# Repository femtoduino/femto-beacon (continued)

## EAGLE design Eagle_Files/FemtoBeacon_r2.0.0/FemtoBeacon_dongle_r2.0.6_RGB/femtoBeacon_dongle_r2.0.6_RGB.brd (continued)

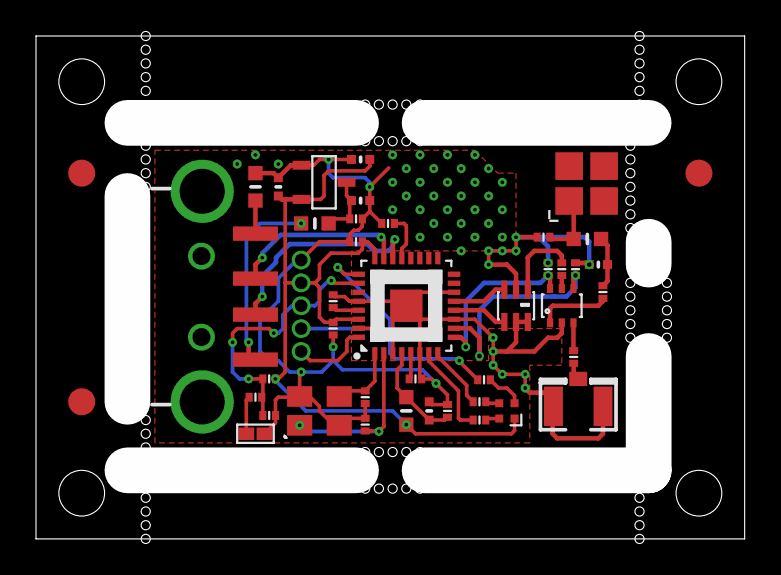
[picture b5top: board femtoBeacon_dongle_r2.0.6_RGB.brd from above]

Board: 2 copper layers, 39.4 x 27.9 mm, 44 parts (0 on the bottom side), 34 nets.

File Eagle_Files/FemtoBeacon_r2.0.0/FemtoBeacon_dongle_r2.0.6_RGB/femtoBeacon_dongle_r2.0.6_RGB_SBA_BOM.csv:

##########################################################################
       Name: Placement Bill of Materials Generator

    Version: 4 (2-sided, top)
         By: Small Batch Assembly
        URL: www.smallbatchassembly.com
 SourceFile: femtoBeacon_dongle_r2.0.6_RGB.brd
   DateTime: 1/3/18 4:22 AM
      Units: inches
##########################################################################
REF,PACKAGE,VALUE,X,Y,ROTATION,
ASWITCH   , AS222-92LF            , AS222-92LF     , 1.1500, 0.5100, 0.0
BTN   , SPST_SMD            , DNP     , 0.4800, 0.2300, 0.0
C1   , PART            , 0.1uF     , 0.5100, 0.2700, 0.0
C2   , PART            , 0.1uF     , 0.7700, 0.6900, 180.0
C5   , _0402MP            , 2.2uF     , 0.7100, 0.8300, 180.0
C6   , _0402MP            , 2.2uF     , 0.7100, 0.7400, 0.0
C7   , PART            , 0.47uF     , 0.7000, 0.7000, 0.0
C8   , PART            , 0.1uF     , 0.9000, 0.2800, 90.0
C9   , PART            , 0.1uF     , 0.6500, 0.5200, 90.0
C10   , PART            , 0.1uF     , 0.7000, 0.6500, 180.0
C11   , _0402MP            , 1.2pF     , 1.2300, 0.6000, 180.0
C13   , PART            , DNP     , 1.1100, 0.6600, 180.0
C14   , PART            , 9pF     , 0.7200, 0.2500, 270.0
C15   , PART            , 9pF     , 0.7200, 0.3100, 270.0
C16   , PART            , 0.1uF     , 0.6500, 0.4600, 270.0
C17   , PART            , 0.1uF     , 0.8300, 0.3500, 0.0
C18   , PART            , 22pF     , 1.1500, 0.5900, 270.0
C19   , PART            , 22pF     , 1.1800, 0.5900, 270.0
C20   , PART            , 22pF     , 1.1200, 0.5900, 90.0
C21   , _0402MP            , 10uF     , 0.5300, 0.7700, 270.0
C22   , _0402MP            , 10uF     , 0.8600, 0.2800, 270.0
C23   , PART            , 22pF     , 1.1760, 0.3980, 90.0
C24   , PART            , 22pF     , 1.2400, 0.5400, 90.0
CN1   , USB_A-SMT            ,      , 0.4800, 0.5300, 90.0
FB1   , _0603MP            ,      , 0.4800, 0.7700, 90.0
FB2   , _0603MP            ,      , 0.6100, 0.6900, 0.0
FID1   , FIDUCIAL_1MM            , FIDUCIAL     , 0.1000, 0.3000, 0.0
FID2   , FIDUCIAL_1MM            , FIDUCIAL     , 0.1000, 0.8000, 0.0
FID3   , FIDUCIAL_1MM            , FIDUCIAL     , 1.4500, 0.8000, 0.0
L1   , _0603MP            , 1.8nH     , 1.2060, 0.6560, 0.0
L6   , _0603MP            , 10uH     , 0.8100, 0.2800, 90.0
LDO_VREG   , MCP1700T-3302E/TT            , MCP1700T-3302E/TT     , 0.6300, 0.7800, 270.0
R1   , PART            , 330     , 0.4800, 0.3100, 0.0
R2   , PART            , 10K     , 0.5100, 0.3500, 0.0
R4   , PART            , 330     , 0.9700, 0.2600, 0.0
R6   , PART            , 330     , 0.9700, 0.3000, 0.0
R7   , PART            , 330     , 0.9800, 0.3480, 0.0
RGBLED   , LRTB_R48G            , LRTB_R48G     , 1.0300, 0.2800, 270.0
U$6   , 0479480001            , 0479480001     , 1.2040, 0.7770, 90.0
U$12   , 0805_BALUN            , JOHANSON_2450BM15A0015E     , 1.0500, 0.5100, 270.0
U$76   , QFN32            , ATSAMR21E18A-MUT     , 0.8100, 0.5100, 90.0
UFLANT   , U.FL            , uFL     , 1.1860, 0.2900, 90.0
XOSCRF   , TSX-3225            , 16MHz     , 0.6200, 0.2800, 0.0

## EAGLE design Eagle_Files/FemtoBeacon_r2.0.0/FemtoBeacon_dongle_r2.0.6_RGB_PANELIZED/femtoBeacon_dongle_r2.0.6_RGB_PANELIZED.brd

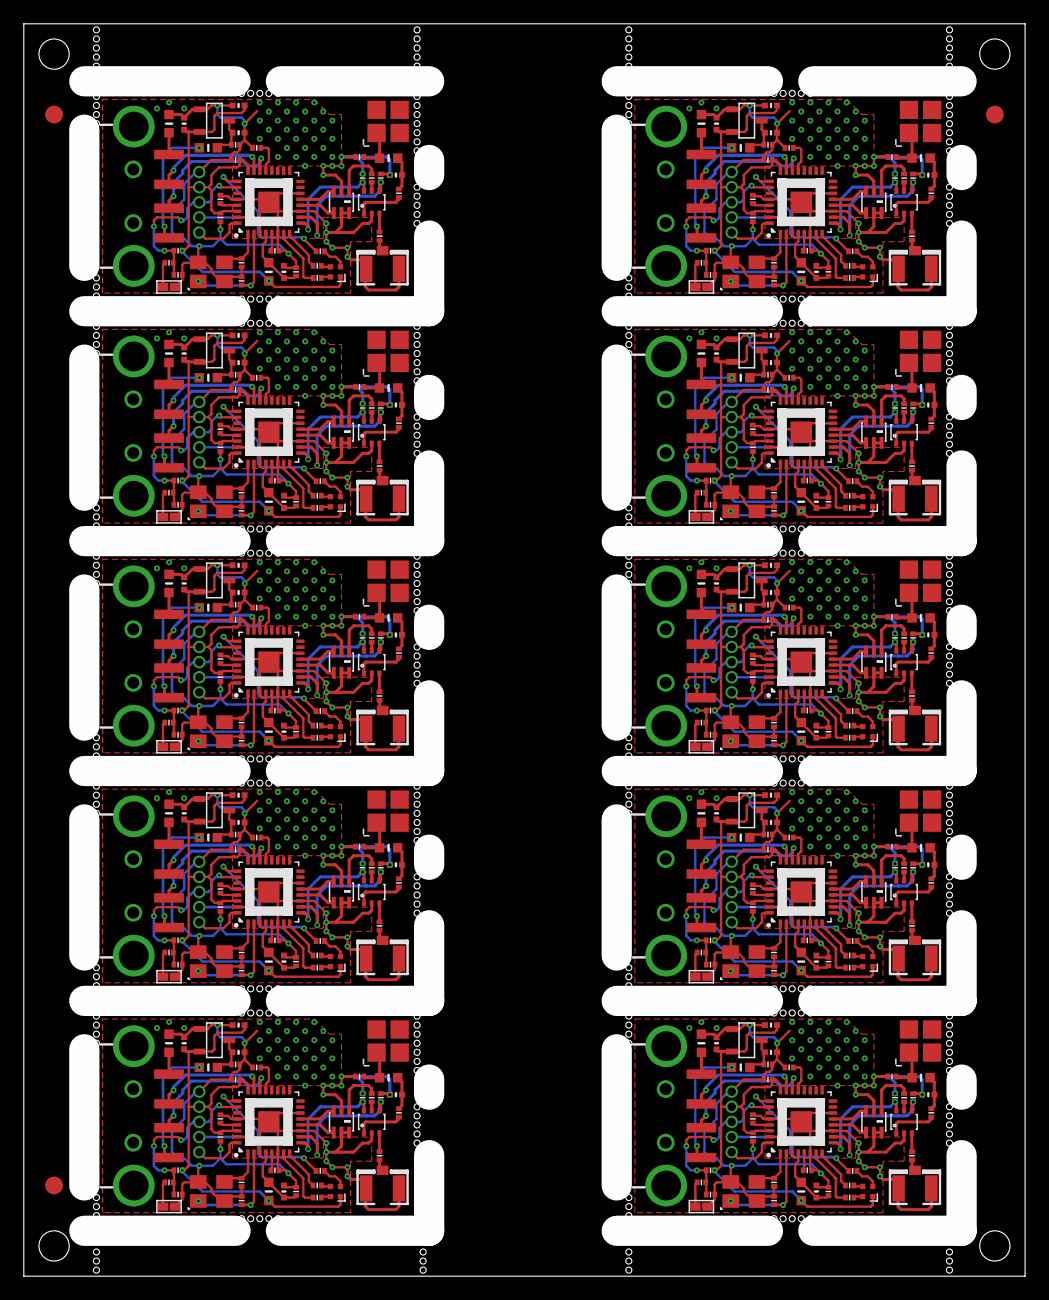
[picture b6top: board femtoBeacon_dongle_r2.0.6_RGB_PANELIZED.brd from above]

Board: 2 copper layers, 84.1 x 105.2 mm, 413 parts (0 on the bottom side), 340 nets.

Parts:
ASWITCH, ASWITCH1, ASWITCH2, ASWITCH3, ASWITCH4, ASWITCH5, ASWITCH6, ASWITCH7, ASWITCH8, ASWITCH9: AS222-92LF
BTN, BTN1, BTN2, BTN3, BTN4, BTN5, BTN6, BTN7, BTN8, BTN9: DNP; SPST_SMD
C1, C2, C3, C4, C8, C9, C10, C16, C17, C27, C28, C29, C35, C36, C43, C44, C48, C49, C50, C56, C57, C64, C65, C69, C70, C71, C77, C78, C85, C86, C90, C91, C92, C98, C99, C106, C107, C111, C112, C113, C119, C120, C127, C128, C132, C133, C134, C140, C141, C148, C149, C153, C154, C155, C161, C162, C169, C170, C174, C175, C176, C182, C183, C190, C191, C195, C196, C197, C203, C204: 0.1uF; PART
C5, C6, C32, C33, C53, C54, C74, C75, C95, C96, C116, C117, C137, C138, C158, C159, C179, C180, C200, C201: 2.2uF; _0402MP
C7, C34, C55, C76, C97, C118, C139, C160, C181, C202: 0.47uF; PART
C11, C42, C63, C84, C105, C126, C147, C168, C189, C210: 1.2pF; _0402MP
C12, C13, C45, C66, C87, C108, C129, C150, C171, C192: DNP; PART
C14, C15, C25, C26, C46, C47, C67, C68, C88, C89, C109, C110, C130, C131, C151, C152, C172, C173, C193, C194: 9pF; PART
C18, C19, C20, C23, C24, C37, C38, C39, C40, C41, C58, C59, C60, C61, C62, C79, C80, C81, C82, C83, C100, C101, C102, C103, C104, C121, C122, C123, C124, C125, C142, C143, C144, C145, C146, C163, C164, C165, C166, C167, C184, C185, C186, C187, C188, C205, C206, C207, C208, C209: 22pF; PART
C21, C22, C30, C31, C51, C52, C72, C73, C93, C94, C114, C115, C135, C136, C156, C157, C177, C178, C198, C199: 10uF; _0402MP
CN1, CN2, CN3, CN4, CN5, CN6, CN7, CN8, CN9, CN10: USB_A-SMT
FB1, FB2, FB3, FB4, FB5, FB6, FB7, FB8, FB9, FB10, FB11, FB12, FB13, FB14, FB15, FB16, FB17, FB18, FB19, FB20: _0603MP
FID1, FID2, FID3: FIDUCIAL; FIDUCIAL_1MM
L1, L3, L5, L8, L10, L12, L14, L16, L18, L20: 1.8nH; _0603MP
L2, L4, L6, L7, L9, L11, L13, L15, L17, L19: 10uH; _0603MP
LDO_VREG, LDO_VREG1, LDO_VREG2, LDO_VREG3, LDO_VREG4, LDO_VREG5, LDO_VREG6, LDO_VREG7, LDO_VREG8, LDO_VREG9: MCP1700T-3302E/TT
R1, R3, R4, R6, R7, R8, R9, R10, R11, R13, R14, R15, R16, R18, R19, R20, R21, R23, R24, R25, R26, R28, R29, R30, R31, R33, R34, R35, R36, R38, R39, R40, R41, R43, R44, R45, R46, R48, R49, R50: 330; PART
R2, R5, R12, R17, R22, R27, R32, R37, R42, R47: 10K; PART
RGBLED, RGBLED1, RGBLED2, RGBLED3, RGBLED4, RGBLED5, RGBLED6, RGBLED7, RGBLED8, RGBLED9: LRTB_R48G
U$1, U$4, U$9, U$14, U$18, U$22, U$26, U$30, U$34, U$38: 1X5_ROUND
U$2, U$7, U$11, U$12, U$16, U$20, U$24, U$28, U$32, U$36: JOHANSON_2450BM15A0015E; 0805_BALUN
U$3, U$8, U$13, U$17, U$21, U$25, U$29, U$33, U$37, U$76: ATSAMR21E18A-MUT; QFN32
U$5, U$6, U$10, U$15, U$19, U$23, U$27, U$31, U$35, U$39: 0479480001
UFLANT, UFLANT1, UFLANT2, UFLANT3, UFLANT4, UFLANT5, UFLANT6, UFLANT7, UFLANT8, UFLANT9: uFL; U.FL
XOSCRF, XOSCRF1, XOSCRF2, XOSCRF3, XOSCRF4, XOSCRF5, XOSCRF6, XOSCRF7, XOSCRF8, XOSCRF9: 16MHz; TSX-3225

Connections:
3.3V: C5.1, C10.1, C16.1, C21.2, L6.1, LDO_VREG.VOUT, R2.2, RGBLED.1, U$1.P$2, U$76.24, U$76.30
3.3V1: C4.1, C27.1, C30.2, C32.1, L2.1, LDO_VREG1.VOUT, R5.2, RGBLED1.1, U$3.24, U$3.30, U$4.P$2
3.3V2: C44.1, C48.1, C51.2, C53.1, L4.1, LDO_VREG2.VOUT, R12.2, RGBLED2.1, U$8.24, U$8.30, U$9.P$2
3.3V3: C65.1, C69.1, C72.2, C74.1, L7.1, LDO_VREG3.VOUT, R17.2, RGBLED3.1, U$13.24, U$13.30, U$14.P$2
3.3V4: C86.1, C90.1, C93.2, C95.1, L9.1, LDO_VREG4.VOUT, R22.2, RGBLED4.1, U$17.24, U$17.30, U$18.P$2
3.3V5: C107.1, C111.1, C114.2, C116.1, L11.1, LDO_VREG5.VOUT, R27.2, RGBLED5.1, U$21.24, U$21.30, U$22.P$2
3.3V6: C128.1, C132.1, C135.2, C137.1, L13.1, LDO_VREG6.VOUT, R32.2, RGBLED6.1, U$25.24, U$25.30, U$26.P$2
3.3V7: C149.1, C153.1, C156.2, C158.1, L15.1, LDO_VREG7.VOUT, R37.2, RGBLED7.1, U$29.24, U$29.30, U$30.P$2
3.3V8: C170.1, C174.1, C177.2, C179.1, L17.1, LDO_VREG8.VOUT, R42.2, RGBLED8.1, U$33.24, U$33.30, U$34.P$2
3.3V9: C191.1, C195.1, C198.2, C200.1, L19.1, LDO_VREG9.VOUT, R47.2, RGBLED9.1, U$37.24, U$37.30, U$38.P$2
ANT_LINE: C13.1, L1.1, U$6.ANT
ANT_LINE1: C12.1, L3.1, U$5.ANT
ANT_LINE2: C45.1, L5.1, U$10.ANT
ANT_LINE3: C66.1, L8.1, U$15.ANT
ANT_LINE4: C87.1, L10.1, U$19.ANT
ANT_LINE5: C108.1, L12.1, U$23.ANT
ANT_LINE6: C129.1, L14.1, U$27.ANT
ANT_LINE7: C150.1, L16.1, U$31.ANT
ANT_LINE8: C171.1, L18.1, U$35.ANT
ANT_LINE9: C192.1, L20.1, U$39.ANT
ANT_OUT: C18.1, U$12.1
ANT_OUT1: C37.1, U$2.1
ANT_OUT2: C58.1, U$7.1
ANT_OUT3: C79.1, U$11.1
ANT_OUT4: C100.1, U$16.1
ANT_OUT5: C121.1, U$20.1
ANT_OUT6: C142.1, U$24.1
ANT_OUT7: C163.1, U$28.1
ANT_OUT8: C184.1, U$32.1
ANT_OUT9: C205.1, U$36.1
ANT_SMD: C11.1, C24.2, L1.2
ANT_SMD1: C41.2, C42.1, L3.2
ANT_SMD2: C62.2, C63.1, L5.2
ANT_SMD3: C83.2, C84.1, L8.2
ANT_SMD4: C104.2, C105.1, L10.2
ANT_SMD5: C125.2, C126.1, L12.2
ANT_SMD6: C146.2, C147.1, L14.2
ANT_SMD7: C167.2, C168.1, L16.2
ANT_SMD8: C188.2, C189.1, L18.2
ANT_SMD9: C209.2, C210.1, L20.2
ANT_UFL: C23.1, UFLANT.3
ANT_UFL1: C40.1, UFLANT1.3
ANT_UFL2: C61.1, UFLANT2.3
ANT_UFL3: C82.1, UFLANT3.3
ANT_UFL4: C103.1, UFLANT4.3
ANT_UFL5: C124.1, UFLANT5.3
ANT_UFL6: C145.1, UFLANT6.3
ANT_UFL7: C166.1, UFLANT7.3
ANT_UFL8: C187.1, UFLANT8.3
ANT_UFL9: C208.1, UFLANT9.3
AVDD: C17.1, U$76.5
AVDD1: C28.1, U$3.5
AVDD2: C49.1, U$8.5
AVDD3: C70.1, U$13.5
AVDD4: C91.1, U$17.5
AVDD5: C112.1, U$21.5
AVDD6: C133.1, U$25.5
AVDD7: C154.1, U$29.5
AVDD8: C175.1, U$33.5
AVDD9: C196.1, U$37.5
DVDD: C2.1, U$76.21
DVDD1: C29.1, U$3.21
DVDD2: C50.1, U$8.21
DVDD3: C71.1, U$13.21
DVDD4: C92.1, U$17.21
DVDD5: C113.1, U$21.21
DVDD6: C134.1, U$25.21
DVDD7: C155.1, U$29.21
DVDD8: C176.1, U$33.21
DVDD9: C197.1, U$37.21
GND: ASWITCH.PIN2, BTN.2, C1.2, C2.2, C5.2, C6.2, C7.2, C8.2, C9.2, C10.2, C11.2, C13.2, C14.1, C15.2, C16.2, C17.2, C19.1, C20.2, C21.1, C22.1, FB1.2, LDO_VREG.GND, U$1.P$1, U$12.2, U$12.5, U$12.6, U$76.3, U$76.6, U$76.11, U$76.14, U$76.28, U$76.33, UFLANT.1, UFLANT.2, XOSCRF.2, XOSCRF.4
GND1: ASWITCH1.PIN2, BTN1.2, C3.2, C4.2, C12.2, C25.1, C26.2, C27.2, C28.2, C29.2, C30.1, C31.1, C32.2, C33.2, C34.2, C35.2, C36.2, C38.1, C39.2, C42.2, FB3.2, LDO_VREG1.GND, U$2.2, U$2.5, U$2.6, U$3.3, U$3.6, U$3.11, U$3.14, U$3.28, U$3.33, U$4.P$1, UFLANT1.1, UFLANT1.2, XOSCRF1.2, XOSCRF1.4
GND2: ASWITCH2.PIN2, BTN2.2, C43.2, C44.2, C45.2, C46.1, C47.2, C48.2, C49.2, C50.2, C51.1, C52.1, C53.2, C54.2, C55.2, C56.2, C57.2, C59.1, C60.2, C63.2, FB5.2, LDO_VREG2.GND, U$7.2, U$7.5, U$7.6, U$8.3, U$8.6, U$8.11, U$8.14, U$8.28, U$8.33, U$9.P$1, UFLANT2.1, UFLANT2.2, XOSCRF2.2, XOSCRF2.4
GND3: ASWITCH3.PIN2, BTN3.2, C64.2, C65.2, C66.2, C67.1, C68.2, C69.2, C70.2, C71.2, C72.1, C73.1, C74.2, C75.2, C76.2, C77.2, C78.2, C80.1, C81.2, C84.2, FB7.2, LDO_VREG3.GND, U$11.2, U$11.5, U$11.6, U$13.3, U$13.6, U$13.11, U$13.14, U$13.28, U$13.33, U$14.P$1, UFLANT3.1, UFLANT3.2, XOSCRF3.2, XOSCRF3.4
GND4: ASWITCH4.PIN2, BTN4.2, C85.2, C86.2, C87.2, C88.1, C89.2, C90.2, C91.2, C92.2, C93.1, C94.1, C95.2, C96.2, C97.2, C98.2, C99.2, C101.1, C102.2, C105.2, FB9.2, LDO_VREG4.GND, U$16.2, U$16.5, U$16.6, U$17.3, U$17.6, U$17.11, U$17.14, U$17.28, U$17.33, U$18.P$1, UFLANT4.1, UFLANT4.2, XOSCRF4.2, XOSCRF4.4
GND5: ASWITCH5.PIN2, BTN5.2, C106.2, C107.2, C108.2, C109.1, C110.2, C111.2, C112.2, C113.2, C114.1, C115.1, C116.2, C117.2, C118.2, C119.2, C120.2, C122.1, C123.2, C126.2, FB11.2, LDO_VREG5.GND, U$20.2, U$20.5, U$20.6, U$21.3, U$21.6, U$21.11, U$21.14, U$21.28, U$21.33, U$22.P$1, UFLANT5.1, UFLANT5.2, XOSCRF5.2, XOSCRF5.4
GND6: ASWITCH6.PIN2, BTN6.2, C127.2, C128.2, C129.2, C130.1, C131.2, C132.2, C133.2, C134.2, C135.1, C136.1, C137.2, C138.2, C139.2, C140.2, C141.2, C143.1, C144.2, C147.2, FB13.2, LDO_VREG6.GND, U$24.2, U$24.5, U$24.6, U$25.3, U$25.6, U$25.11, U$25.14, U$25.28, U$25.33, U$26.P$1, UFLANT6.1, UFLANT6.2, XOSCRF6.2, XOSCRF6.4
GND7: ASWITCH7.PIN2, BTN7.2, C148.2, C149.2, C150.2, C151.1, C152.2, C153.2, C154.2, C155.2, C156.1, C157.1, C158.2, C159.2, C160.2, C161.2, C162.2, C164.1, C165.2, C168.2, FB15.2, LDO_VREG7.GND, U$28.2, U$28.5, U$28.6, U$29.3, U$29.6, U$29.11, U$29.14, U$29.28, U$29.33, U$30.P$1, UFLANT7.1, UFLANT7.2, XOSCRF7.2, XOSCRF7.4
GND8: ASWITCH8.PIN2, BTN8.2, C169.2, C170.2, C171.2, C172.1, C173.2, C174.2, C175.2, C176.2, C177.1, C178.1, C179.2, C180.2, C181.2, C182.2, C183.2, C185.1, C186.2, C189.2, FB17.2, LDO_VREG8.GND, U$32.2, U$32.5, U$32.6, U$33.3, U$33.6, U$33.11, U$33.14, U$33.28, U$33.33, U$34.P$1, UFLANT8.1, UFLANT8.2, XOSCRF8.2, XOSCRF8.4
GND9: ASWITCH9.PIN2, BTN9.2, C190.2, C191.2, C192.2, C193.1, C194.2, C195.2, C196.2, C197.2, C198.1, C199.1, C200.2, C201.2, C202.2, C203.2, C204.2, C206.1, C207.2, C210.2, FB19.2, LDO_VREG9.GND, U$36.2, U$36.5, U$36.6, U$37.3, U$37.6, U$37.11, U$37.14, U$37.28, U$37.33, U$38.P$1, UFLANT9.1, UFLANT9.2, XOSCRF9.2, XOSCRF9.4
unnamed: BTN1.1, R3.1
unnamed: R6.2, RGBLED.3
unnamed: CN2.GND, FB3.1
unnamed: CN1.VBUS, FB2.1
unnamed: CN1.GND, FB1.1
unnamed: CN2.VBUS, FB4.1
unnamed: R8.2, RGBLED1.2
unnamed: R9.2, RGBLED1.3
unnamed: R10.2, RGBLED1.4
unnamed: R7.2, RGBLED.4
unnamed: BTN2.1, R11.1
unnamed: CN3.GND, FB5.1
unnamed: R4.2, RGBLED.2
unnamed: CN3.VBUS, FB6.1
unnamed: R13.2, RGBLED2.2
unnamed: R14.2, RGBLED2.3
unnamed: R15.2, RGBLED2.4
unnamed: BTN3.1, R16.1
unnamed: CN4.GND, FB7.1
unnamed: CN4.VBUS, FB8.1
unnamed: R18.2, RGBLED3.2
unnamed: R19.2, RGBLED3.3
unnamed: R20.2, RGBLED3.4
unnamed: BTN4.1, R21.1
unnamed: CN5.GND, FB9.1
unnamed: BTN.1, R1.1
unnamed: CN5.VBUS, FB10.1
unnamed: R23.2, RGBLED4.2
unnamed: R24.2, RGBLED4.3
unnamed: R25.2, RGBLED4.4
unnamed: BTN5.1, R26.1
unnamed: CN6.GND, FB11.1
unnamed: CN6.VBUS, FB12.1
unnamed: R28.2, RGBLED5.2
unnamed: R29.2, RGBLED5.3
unnamed: R30.2, RGBLED5.4
unnamed: BTN6.1, R31.1
unnamed: CN7.GND, FB13.1
unnamed: CN7.VBUS, FB14.1
unnamed: R33.2, RGBLED6.2
unnamed: R34.2, RGBLED6.3
unnamed: R35.2, RGBLED6.4
unnamed: BTN7.1, R36.1
unnamed: CN8.GND, FB15.1
unnamed: CN8.VBUS, FB16.1
unnamed: R38.2, RGBLED7.2
unnamed: R39.2, RGBLED7.3
unnamed: R40.2, RGBLED7.4
unnamed: BTN8.1, R41.1
unnamed: CN9.GND, FB17.1
unnamed: CN9.VBUS, FB18.1
unnamed: R43.2, RGBLED8.2
unnamed: R44.2, RGBLED8.3
unnamed: R45.2, RGBLED8.4
unnamed: BTN9.1, R46.1
unnamed: CN10.GND, FB19.1
unnamed: CN10.VBUS, FB20.1
unnamed: R48.2, RGBLED9.2
unnamed: R49.2, RGBLED9.3
unnamed: R50.2, RGBLED9.4
PA06(R): R4.1, U$76.7
PA06(R)1: R8.1, U$3.7
PA06(R)2: R13.1, U$8.7
PA06(R)3: R18.1, U$13.7
PA06(R)4: R23.1, U$17.7
PA06(R)5: R28.1, U$21.7
PA06(R)6: R33.1, U$25.7
PA06(R)7: R38.1, U$29.7
PA06(R)8: R43.1, U$33.7
PA06(R)9: R48.1, U$37.7
PA07(G): R6.1, U$76.8
PA07(G)1: R9.1, U$3.8
PA07(G)2: R14.1, U$8.8
PA07(G)3: R19.1, U$13.8
PA07(G)4: R24.1, U$17.8
PA07(G)5: R29.1, U$21.8
PA07(G)6: R34.1, U$25.8
PA07(G)7: R39.1, U$29.8
PA07(G)8: R44.1, U$33.8
PA07(G)9: R49.1, U$37.8
PA08/I2C/SDA: ASWITCH.PIN6, C20.1, U$76.9
PA08/I2C/SDA1: ASWITCH1.PIN6, C39.1, U$3.9
PA08/I2C/SDA2: ASWITCH2.PIN6, C60.1, U$8.9
PA08/I2C/SDA3: ASWITCH3.PIN6, C81.1, U$13.9
PA08/I2C/SDA4: ASWITCH4.PIN6, C102.1, U$17.9
PA08/I2C/SDA5: ASWITCH5.PIN6, C123.1, U$21.9
PA08/I2C/SDA6: ASWITCH6.PIN6, C144.1, U$25.9
PA08/I2C/SDA7: ASWITCH7.PIN6, C165.1, U$29.9
PA08/I2C/SDA8: ASWITCH8.PIN6, C186.1, U$33.9
PA08/I2C/SDA9: ASWITCH9.PIN6, C207.1, U$37.9
PA09/I2C/SCL: ASWITCH.PIN4, C19.2, U$76.10
PA09/I2C/SCL1: ASWITCH1.PIN4, C38.2, U$3.10
PA09/I2C/SCL2: ASWITCH2.PIN4, C59.2, U$8.10
PA09/I2C/SCL3: ASWITCH3.PIN4, C80.2, U$13.10
PA09/I2C/SCL4: ASWITCH4.PIN4, C101.2, U$17.10
PA09/I2C/SCL5: ASWITCH5.PIN4, C122.2, U$21.10
PA09/I2C/SCL6: ASWITCH6.PIN4, C143.2, U$25.10
PA09/I2C/SCL7: ASWITCH7.PIN4, C164.2, U$29.10
PA09/I2C/SCL8: ASWITCH8.PIN4, C185.2, U$33.10
PA09/I2C/SCL9: ASWITCH9.PIN4, C206.2, U$37.10
PA24/USBDM: CN1.D-, U$76.22
PA24/USBDM1: CN2.D-, U$3.22
PA24/USBDM2: CN3.D-, U$8.22
PA24/USBDM3: CN4.D-, U$13.22
PA24/USBDM4: CN5.D-, U$17.22
PA24/USBDM5: CN6.D-, U$21.22
PA24/USBDM6: CN7.D-, U$25.22
PA24/USBDM7: CN8.D-, U$29.22
PA24/USBDM8: CN9.D-, U$33.22
PA24/USBDM9: CN10.D-, U$37.22
PA25/USBDP: CN1.D+, U$76.23
PA25/USBDP1: CN2.D+, U$3.23
PA25/USBDP2: CN3.D+, U$8.23
PA25/USBDP3: CN4.D+, U$13.23
PA25/USBDP4: CN5.D+, U$17.23
PA25/USBDP5: CN6.D+, U$21.23
PA25/USBDP6: CN7.D+, U$25.23
PA25/USBDP7: CN8.D+, U$29.23
PA25/USBDP8: CN9.D+, U$33.23
PA25/USBDP9: CN10.D+, U$37.23
PA27(B): R7.1, U$76.25
PA27(B)1: R10.1, U$3.25
PA27(B)2: R15.1, U$8.25
PA27(B)3: R20.1, U$13.25
PA27(B)4: R25.1, U$17.25
PA27(B)5: R30.1, U$21.25
PA27(B)6: R35.1, U$25.25
PA27(B)7: R40.1, U$29.25
PA27(B)8: R45.1, U$33.25
PA27(B)9: R50.1, U$37.25
PA30/SWCLK: U$1.P$4, U$76.31
PA30/SWCLK1: U$3.31, U$4.P$4
PA30/SWCLK2: U$8.31, U$9.P$4
PA30/SWCLK3: U$13.31, U$14.P$4
PA30/SWCLK4: U$17.31, U$18.P$4
PA30/SWCLK5: U$21.31, U$22.P$4
PA30/SWCLK6: U$25.31, U$26.P$4
PA30/SWCLK7: U$29.31, U$30.P$4
PA30/SWCLK8: U$33.31, U$34.P$4
PA30/SWCLK9: U$37.31, U$38.P$4
PA31/SWDIO: U$1.P$5, U$76.32
PA31/SWDIO1: U$3.32, U$4.P$5
PA31/SWDIO2: U$8.32, U$9.P$5
PA31/SWDIO3: U$13.32, U$14.P$5
PA31/SWDIO4: U$17.32, U$18.P$5
PA31/SWDIO5: U$21.32, U$22.P$5
PA31/SWDIO6: U$25.32, U$26.P$5
PA31/SWDIO7: U$29.32, U$30.P$5
PA31/SWDIO8: U$33.32, U$34.P$5
PA31/SWDIO9: U$37.32, U$38.P$5
RESET: C1.1, R1.2, R2.1, U$1.P$3, U$76.26
RESET1: C3.1, R3.2, R5.1, U$3.26, U$4.P$3
RESET2: C43.1, R11.2, R12.1, U$8.26, U$9.P$3
RESET3: C64.1, R16.2, R17.1, U$13.26, U$14.P$3
RESET4: C85.1, R21.2, R22.1, U$17.26, U$18.P$3
RESET5: C106.1, R26.2, R27.1, U$21.26, U$22.P$3
RESET6: C127.1, R31.2, R32.1, U$25.26, U$26.P$3
RESET7: C148.1, R36.2, R37.1, U$29.26, U$30.P$3
RESET8: C169.1, R41.2, R42.1, U$33.26, U$34.P$3
RESET9: C190.1, R46.2, R47.1, U$37.26, U$38.P$3
RFN: U$12.3, U$76.13
RFN1: U$2.3, U$3.13
RFN2: U$7.3, U$8.13
RFN3: U$11.3, U$13.13
RFN4: U$16.3, U$17.13
RFN5: U$20.3, U$21.13
RFN6: U$24.3, U$25.13
RFN7: U$28.3, U$29.13
RFN8: U$32.3, U$33.13
RFN9: U$36.3, U$37.13
RFP: U$12.4, U$76.12
RFP1: U$2.4, U$3.12
RFP2: U$7.4, U$8.12
RFP3: U$11.4, U$13.12
RFP4: U$16.4, U$17.12
RFP5: U$20.4, U$21.12
RFP6: U$24.4, U$25.12
RFP7: U$28.4, U$29.12
RFP8: U$32.4, U$33.12
RFP9: U$36.4, U$37.12
RFSWITCH_PIN1: ASWITCH.PIN1, C24.1
RFSWITCH_PIN2: ASWITCH1.PIN1, C41.1
RFSWITCH_PIN3: ASWITCH.PIN3, C23.2
RFSWITCH_PIN4: ASWITCH1.PIN5, C37.2
RFSWITCH_PIN5: ASWITCH.PIN5, C18.2
RFSWITCH_PIN6: ASWITCH1.PIN3, C40.2
RFSWITCH_PIN7: ASWITCH2.PIN1, C62.1
RFSWITCH_PIN8: ASWITCH2.PIN5, C58.2
RFSWITCH_PIN9: ASWITCH2.PIN3, C61.2
RFSWITCH_PIN10: ASWITCH3.PIN1, C83.1
RFSWITCH_PIN11: ASWITCH3.PIN5, C79.2
RFSWITCH_PIN12: ASWITCH3.PIN3, C82.2
RFSWITCH_PIN13: ASWITCH4.PIN1, C104.1
RFSWITCH_PIN14: ASWITCH4.PIN5, C100.2
RFSWITCH_PIN15: ASWITCH4.PIN3, C103.2
RFSWITCH_PIN16: ASWITCH5.PIN1, C125.1
RFSWITCH_PIN17: ASWITCH5.PIN5, C121.2
RFSWITCH_PIN18: ASWITCH5.PIN3, C124.2
RFSWITCH_PIN19: ASWITCH6.PIN1, C146.1
RFSWITCH_PIN20: ASWITCH6.PIN5, C142.2
RFSWITCH_PIN21: ASWITCH6.PIN3, C145.2
RFSWITCH_PIN22: ASWITCH7.PIN1, C167.1
RFSWITCH_PIN23: ASWITCH7.PIN5, C163.2
RFSWITCH_PIN24: ASWITCH7.PIN3, C166.2
RFSWITCH_PIN25: ASWITCH8.PIN1, C188.1
RFSWITCH_PIN26: ASWITCH8.PIN5, C184.2
RFSWITCH_PIN27: ASWITCH8.PIN3, C187.2
RFSWITCH_PIN28: ASWITCH9.PIN1, C209.1
RFSWITCH_PIN29: ASWITCH9.PIN5, C205.2
RFSWITCH_PIN30: ASWITCH9.PIN3, C208.2
VDDANA: C8.1, C22.2, L6.2, U$76.4
VDDANA1: C31.2, C35.1, L2.2, U$3.4
VDDANA2: C52.2, C56.1, L4.2, U$8.4
VDDANA3: C73.2, C77.1, L7.2, U$13.4
VDDANA4: C94.2, C98.1, L9.2, U$17.4
VDDANA5: C115.2, C119.1, L11.2, U$21.4
VDDANA6: C136.2, C140.1, L13.2, U$25.4
VDDANA7: C157.2, C161.1, L15.2, U$29.4
VDDANA8: C178.2, C182.1, L17.2, U$33.4
VDDANA9: C199.2, C203.1, L19.2, U$37.4
VDDCORE: C9.1, U$76.29
VDDCORE1: C36.1, U$3.29
VDDCORE2: C57.1, U$8.29
VDDCORE3: C78.1, U$13.29
VDDCORE4: C99.1, U$17.29
VDDCORE5: C120.1, U$21.29
VDDCORE6: C141.1, U$25.29
VDDCORE7: C162.1, U$29.29
VDDCORE8: C183.1, U$33.29
VDDCORE9: C204.1, U$37.29
VIN: C6.1, C7.1, FB2.2, LDO_VREG.VIN
VIN1: C33.1, C34.1, FB4.2, LDO_VREG1.VIN
VIN2: C54.1, C55.1, FB6.2, LDO_VREG2.VIN
VIN3: C75.1, C76.1, FB8.2, LDO_VREG3.VIN
VIN4: C96.1, C97.1, FB10.2, LDO_VREG4.VIN
VIN5: C117.1, C118.1, FB12.2, LDO_VREG5.VIN
VIN6: C138.1, C139.1, FB14.2, LDO_VREG6.VIN
VIN7: C159.1, C160.1, FB16.2, LDO_VREG7.VIN
VIN8: C180.1, C181.1, FB18.2, LDO_VREG8.VIN
VIN9: C201.1, C202.1, FB20.2, LDO_VREG9.VIN
XTALIN: C14.2, U$76.2, XOSCRF.1
XTALIN1: C25.2, U$3.2, XOSCRF1.1
XTALIN2: C46.2, U$8.2, XOSCRF2.1
XTALIN3: C67.2, U$13.2, XOSCRF3.1
XTALIN4: C88.2, U$17.2, XOSCRF4.1
XTALIN5: C109.2, U$21.2, XOSCRF5.1
XTALIN6: C130.2, U$25.2, XOSCRF6.1
XTALIN7: C151.2, U$29.2, XOSCRF7.1
XTALIN8: C172.2, U$33.2, XOSCRF8.1
XTALIN9: C193.2, U$37.2, XOSCRF9.1
XTALOUT: C15.1, U$76.1, XOSCRF.3
XTALOUT1: C26.1, U$3.1, XOSCRF1.3
XTALOUT2: C47.1, U$8.1, XOSCRF2.3
XTALOUT3: C68.1, U$13.1, XOSCRF3.3
XTALOUT4: C89.1, U$17.1, XOSCRF4.3
XTALOUT5: C110.1, U$21.1, XOSCRF5.3
XTALOUT6: C131.1, U$25.1, XOSCRF6.3
XTALOUT7: C152.1, U$29.1, XOSCRF7.3
XTALOUT8: C173.1, U$33.1, XOSCRF8.3
XTALOUT9: C194.1, U$37.1, XOSCRF9.3

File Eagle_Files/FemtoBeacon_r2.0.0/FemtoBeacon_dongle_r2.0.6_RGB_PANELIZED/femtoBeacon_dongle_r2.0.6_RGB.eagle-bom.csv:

Qty,Value,Device,Package,Parts,Description,MFR_ID
2,,FERRITE_0603MP,_0603MP,"FB1, FB2",Ferrite Bead,BLM18RK102SN1D
1,,USB_TYPEA,USB_A-SMT,CN1,USB - Type A Connectors,Keystone 931
7,0.1uF,CAPACITOR_0201,PART,"C1, C2, C8, C9, C10, C16, C17",,GRM033C80J104KE84D
1,0.47uF,CAPACITOR_0201,PART,C7,,C0603X5R0J474K030BC
1,479480001,479480001,479480001,U$6,,51T4020
1,1.2pF,CAP_CERAMIC_0402MP,_0402MP,C11,Ceramic Capacitors,GRM1555C1H1R2BA01D
1,1.8nH,INDUCTOR_0603MP,_0603MP,L1,Inductors,L-14C1N8SV4T
1,10K,RESISTOR_0201,PART,R2,,RC0402FR-0710KL
2,10uF,CAP_CERAMIC_0402MP,_0402MP,"C21, C22",Ceramic Capacitors,AMK105CBJ106MV-F
1,10uH,INDUCTOR_0603MP,_0603MP,L6,Inductors,LQM18FN100M00D
1,16MHz,TSX-3225,TSX-3225,XOSCRF,,TSX-3225 16.0000MF09Z-AC0
1,DNP,1X5_ROUND,1X5_ROUND,U$1,,
2,2.2uF,CAP_CERAMIC_0402MP,_0402MP,"C5, C6",Ceramic Capacitors,C1005X5R1A225K050BC
5,22pF,CAPACITOR_0201,PART,"C18, C19, C20, C23, C24",,GRM0335C1E220JA01D
4,330,RESISTOR_0201,PART,"R1, R4, R6, R7",,CRCW0201330RJNED
2,9pF,CAPACITOR_0201,PART,"C14, C15",,C0603C0G1E090B030BG
1,AS222-92LF,AS222-92LF,AS222-92LF,ASWITCH,,AS222-92LF
1,ATSAMR21E18A-MUT,ATSAMR21E18A-MUT,QFN32,U$76,This is the ATMEL SAMR21E QFN-32. ATSAMR21E18A,ATSAMR21E18A-MFT
1,DNP,CAPACITOR_0201,PART,C13,,
1,DNP,SPST_SMD,SPST_SMD,BTN,,
3,FIDUCIAL,FIDUCIAL,FIDUCIAL_1MM,"FID1, FID2, FID3","For use by pick and place machines to calibrate the vision/machine, 1mm",
1,JOHANSON_2450BM15A0015E,JOHANSON_2450BM15A0015E,0805_BALUN,U$12,,2450BM15A0015E
1,LRTB_R48G,LRTB_R48G,LRTB_R48G,RGBLED,,LRTB R48G
1,MCP1700T-3302E/TT,MCP1700T-3302E/TT,MCP1700T-3302E/TT,LDO_VREG,"Microchip LDO ""MCP1700"" in a 3-Pin SOT-23 package.",MCP1700T-3302E/TT
1,uFL,ANTENNA_U.FL,U.FL,UFLANT,U.FL Antenna Connector,734120110

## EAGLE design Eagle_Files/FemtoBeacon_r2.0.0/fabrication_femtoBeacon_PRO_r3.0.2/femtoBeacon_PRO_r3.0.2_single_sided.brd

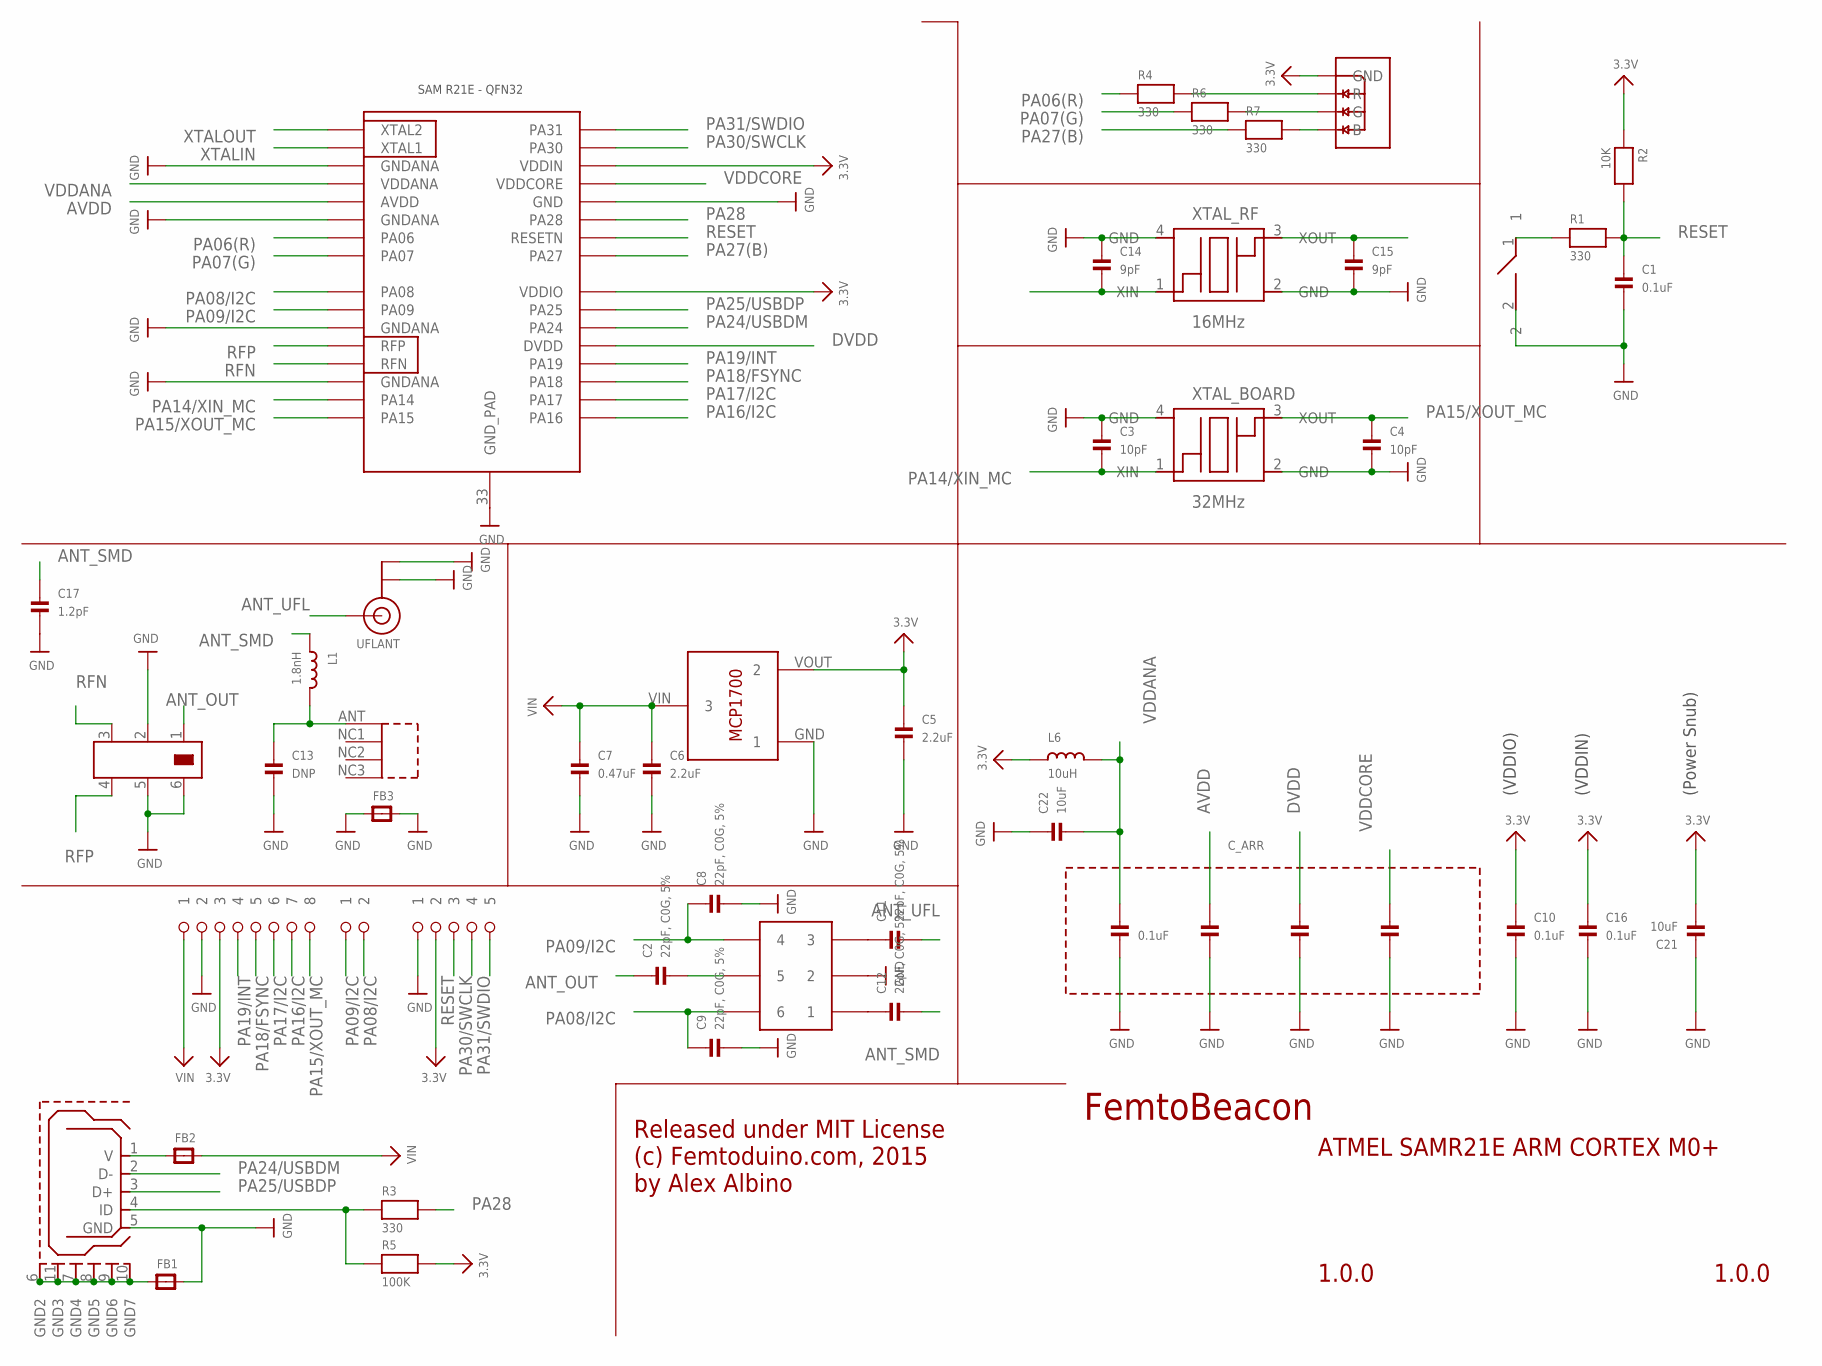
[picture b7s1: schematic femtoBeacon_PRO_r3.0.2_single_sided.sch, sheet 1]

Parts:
ASWITCH: AS222-92LF
BALUN: JOHANSON_2450BM15A0015E; 0805_BALUN
BTN_RESET: DNP; SPST_SMD
C1, C10, C16: 0.1uF; _0402MP; DIGIKEY_PART 490-3194-1-ND
C2, C8, C9, C11, C12: 22pF, C0G, 5%; _0402MP; DIGIKEY_PART 490-3194-1-ND
C3, C4: 10pF; _0402MP; DIGIKEY_PART 490-3194-1-ND
C5, C6: 2.2uF; _0402MP
C7: 0.47uF; _0402MP
C13: DNP; _0402MP; DIGIKEY_PART 490-3194-1-ND
C14, C15: 9pF; _0402MP; DIGIKEY_PART 490-3194-1-ND
C17: 1.2pF; _0402MP
C21, C22: 10uF; _0402MP
C_ARR: 0.1uF; CAPACITOR_ARRAY_1206_MONO_1X4
FB1, FB2, FB3: FERRITE_0603MP; _0603MP
IC: ATSAMR21E18A-MUT; QFN32
L1: 1.8nH; _0603MP
L6: 10uH; _0603MP
LDO_VREG: MCP1700T-3302E/TT
R1, R3, R4, R6, R7: 330; _0402MP
R2: 10K; _0402MP
R5: 100K; _0402MP
RGBLED: LRTB_R48G
U$5: 1X8_ROUND
U$9: 1X2_ROUND
U$10: 1X5_ROUND
U$12: 0479480001
UFLANT: ANTENNA_U.FL; U.FL
USB: USB_MICROB; USB_MICROB_PACKAGE
XTAL_BOARD: 32MHz; FA-128
XTAL_RF: 16MHz; TSX-3225

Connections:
3.3V: C5.1, C10.1, C16.1, C21.2, IC.24 (VDDIO), IC.30 (VDDIN), L6.1, LDO_VREG.VOUT (2), R2.1, R5.2, RGBLED.1 (GND), U$5.P$3 (3), U$10.P$2 (2); also elsewhere on the board
ANT_OUT: BALUN.1, C2.1
ANT_SMD: C12.2, C17.1, L1.1
ANT_UFL: C11.2, UFLANT.3 (SIGNAL)
AVDD: C_ARR.3, IC.5 (AVDD)
DVDD: C_ARR.5, IC.21 (DVDD)
GND: ASWITCH.PIN2 (2), BALUN.2, BALUN.5, BALUN.6, BTN_RESET.2, C1.2, C3.1, C4.2, C5.2, C6.2, C7.2, C8.2, C9.2, C10.2, C13.2, C14.1, C15.2, C16.2, C17.2, C21.1, C22.1, C_ARR.2, C_ARR.4, C_ARR.6, C_ARR.8, FB1.2, FB3.1, FB3.2, IC.3 (GNDANA), IC.6 (GNDANA), IC.11 (GNDANA), IC.14 (GNDANA), IC.28 (GND), IC.33 (GND_PAD), LDO_VREG.GND (1), U$5.P$2 (2), U$10.P$1 (1), UFLANT.1 (GND), UFLANT.2 (GND), USB.5 (GND), XTAL_BOARD.2 (GND), XTAL_BOARD.4 (GND), XTAL_RF.2 (GND), XTAL_RF.4 (GND); also elsewhere on the board
unnamed: C13.1, L1.2, U$12.ANT (1)
unnamed: ASWITCH.PIN5 (5), C2.2
unnamed: FB1.1, USB.6 (GND2), USB.7 (GND4), USB.8 (GND5), USB.9 (GND6), USB.10 (GND7), USB.11 (GND3)
unnamed: R3.1, R5.1, USB.4 (ID)
unnamed: FB2.1, USB.1 (V)
unnamed: R6.2, RGBLED.3 (G)
unnamed: R7.2, RGBLED.4 (B)
unnamed: ASWITCH.PIN3 (3), C11.1
unnamed: ASWITCH.PIN1 (1), C12.1
unnamed: R4.2, RGBLED.2 (R)
unnamed: BTN_RESET.1, R1.1
PA06(R): IC.7 (PA06), R4.1
PA07(G): IC.8 (PA07), R6.1
PA08/I2C: ASWITCH.PIN6 (6), C9.1, IC.9 (PA08), U$9.P$2 (2)
PA09/I2C: ASWITCH.PIN4 (4), C8.1, IC.10 (PA09), U$9.P$1 (1)
PA14/XIN_MC: C3.2, IC.15 (PA14), XTAL_BOARD.1 (XIN)
PA15/XOUT_MC: C4.1, IC.16 (PA15), U$5.P$8 (8), XTAL_BOARD.3 (XOUT)
PA16/I2C: IC.17 (PA16), U$5.P$7 (7); also elsewhere on the board
PA17/I2C: IC.18 (PA17), U$5.P$6 (6); also elsewhere on the board
PA18/FSYNC: IC.19 (PA18), U$5.P$5 (5); also elsewhere on the board
PA19/INT: IC.20 (PA19), U$5.P$4 (4); also elsewhere on the board
PA24/USBDM: IC.22 (PA24), USB.2 (D-)
PA25/USBDP: IC.23 (PA25), USB.3 (D+)
PA27(B): IC.25 (PA27), R7.1
PA28: IC.27 (PA28), R3.2
PA30/SWCLK: IC.31 (PA30), U$10.P$4 (4)
PA31/SWDIO: IC.32 (PA31), U$10.P$5 (5)
RESET: C1.1, IC.26 (RESETN), R1.2, R2.2, U$10.P$3 (3)
RFN: BALUN.3, IC.13 (RFN)
RFP: BALUN.4, IC.12 (RFP)
VDDANA: C22.2, C_ARR.1, IC.4 (VDDANA), L6.2
VDDCORE: C_ARR.7, IC.29 (VDDCORE)
VIN: C6.1, C7.1, FB2.2, LDO_VREG.VIN (3), U$5.P$1 (1)
XTALIN: C14.2, IC.2 (XTAL1), XTAL_RF.1 (XIN)
XTALOUT: C15.1, IC.1 (XTAL2), XTAL_RF.3 (XOUT)

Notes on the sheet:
FemtoBeacon
1.0.0
ATMEL SAMR21E ARM CORTEX M0+
Released under MIT License (c) Femtoduino.com, 2015 by Alex Albino
(Power Snub)
(VDDIO)
(VDDIN)

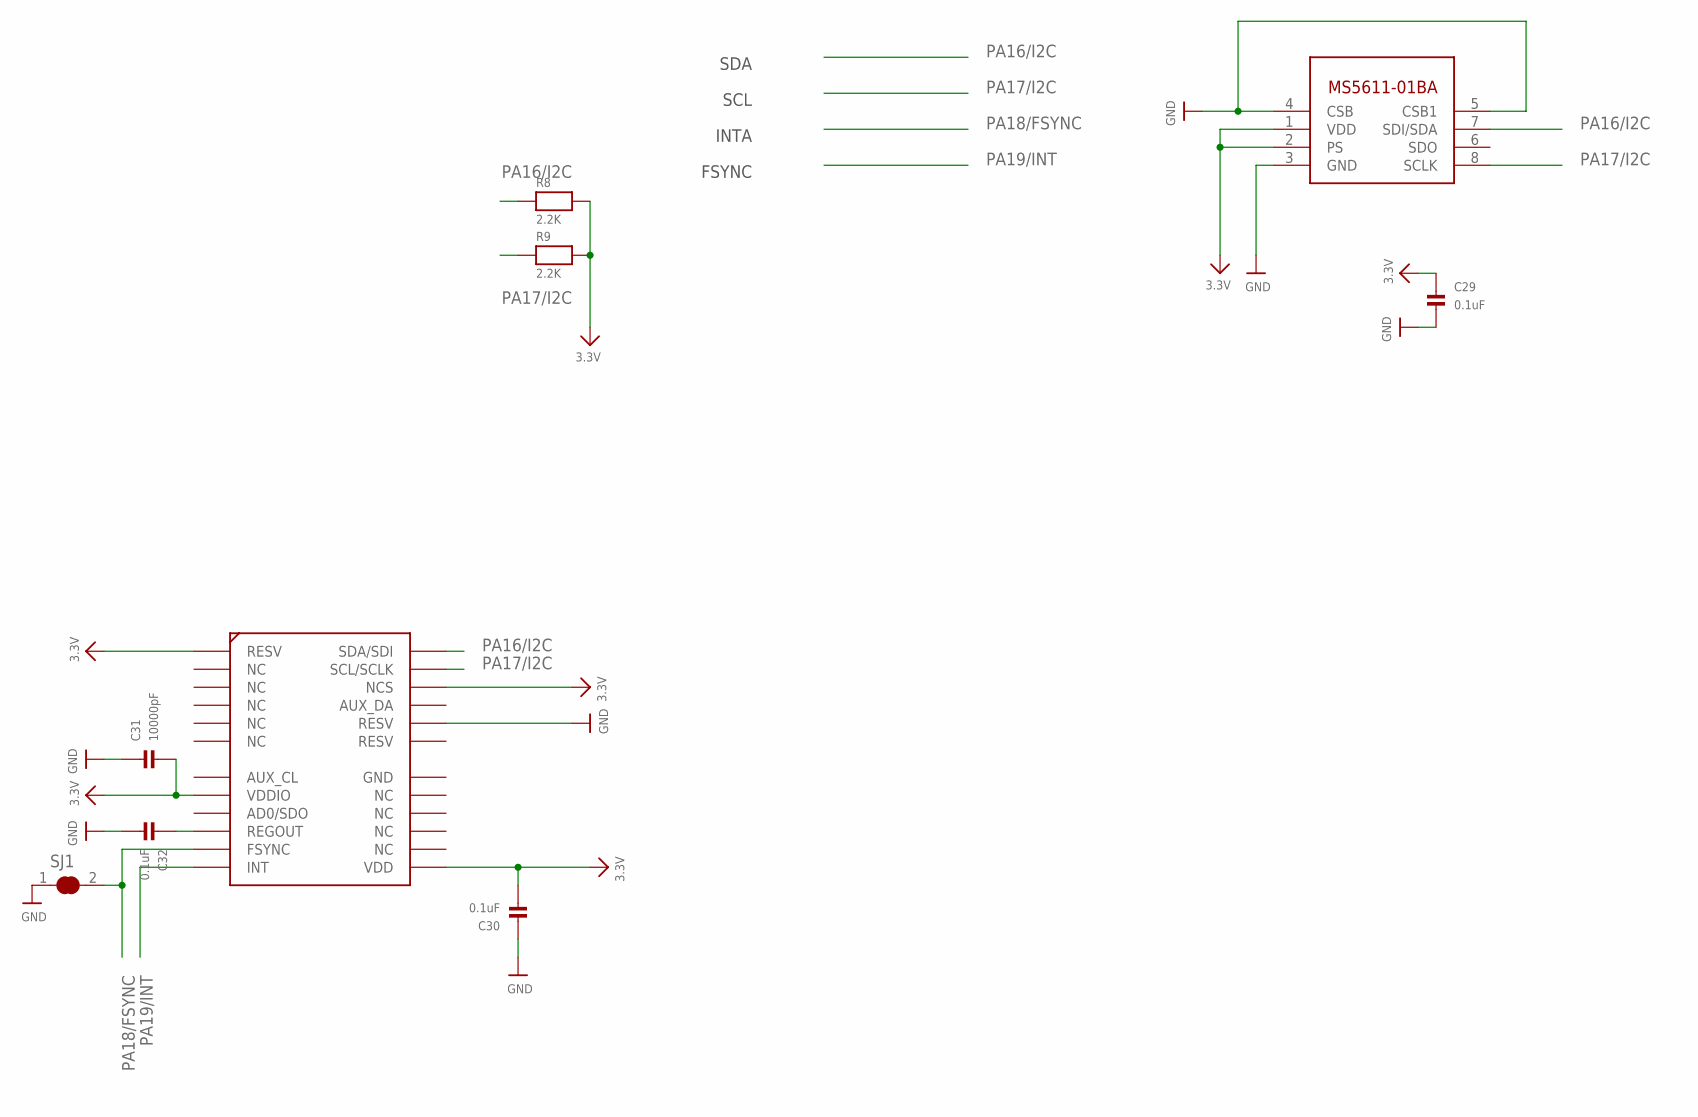
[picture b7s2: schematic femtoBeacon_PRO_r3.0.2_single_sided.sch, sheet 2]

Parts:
BARO: MS5611-01BA03
C29, C30, C32: 0.1uF; _0402MP; DIGIKEY_PART 490-3194-1-ND
C31: 10000pF; _0402MP; DIGIKEY_PART 490-3194-1-ND
IMU: MPU-9250; QFN_3X3MM
R8, R9: 2.2K; _0402MP
SJ1: SOLDERJUMPER_CLOSED; SOLDERJUMPER_CLOSEDWIRE

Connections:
3.3V: BARO.1 (VDD), BARO.2 (PS), C29.1, C30.2, C31.2, IMU.P$1 (RESV), IMU.P$8 (VDDIO), IMU.P$13 (VDD), IMU.P$22 (NCS), R8.2, R9.2; also elsewhere on the board
GND: BARO.3 (GND), BARO.4 (CSB), BARO.5 (CSB1), C29.2, C30.1, C31.1, C32.2, IMU.P$20 (RESV), SJ1.1; also elsewhere on the board
unnamed: C32.1, IMU.P$10 (REGOUT)
PA16/I2C: BARO.7 (SDI/SDA), IMU.P$24 (SDA/SDI), R8.1; also elsewhere on the board
PA17/I2C: BARO.8 (SCLK), IMU.P$23 (SCL/SCLK), R9.1; also elsewhere on the board
PA18/FSYNC: IMU.P$11 (FSYNC), SJ1.2; also elsewhere on the board
PA19/INT: IMU.P$12 (INT); also elsewhere on the board

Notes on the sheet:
SDA
SCL
INTA
FSYNC
